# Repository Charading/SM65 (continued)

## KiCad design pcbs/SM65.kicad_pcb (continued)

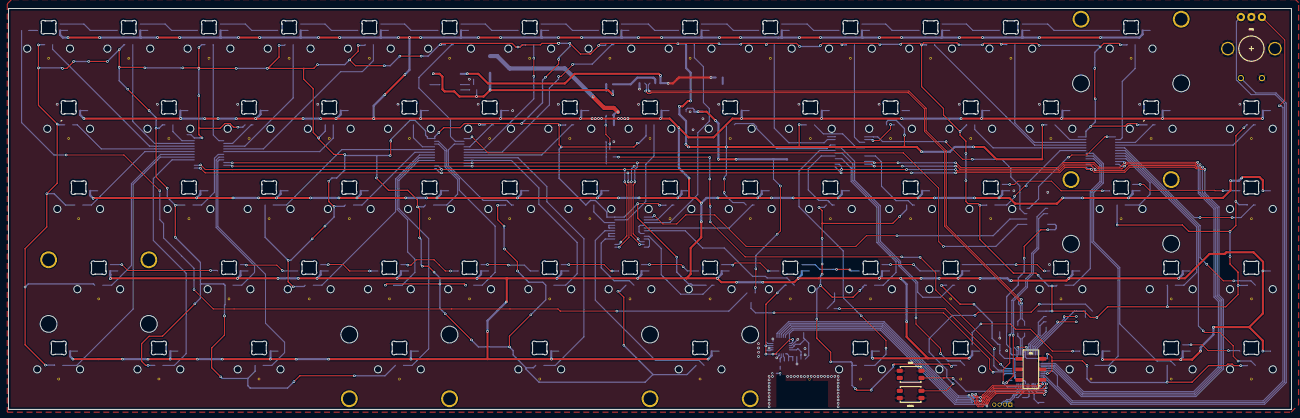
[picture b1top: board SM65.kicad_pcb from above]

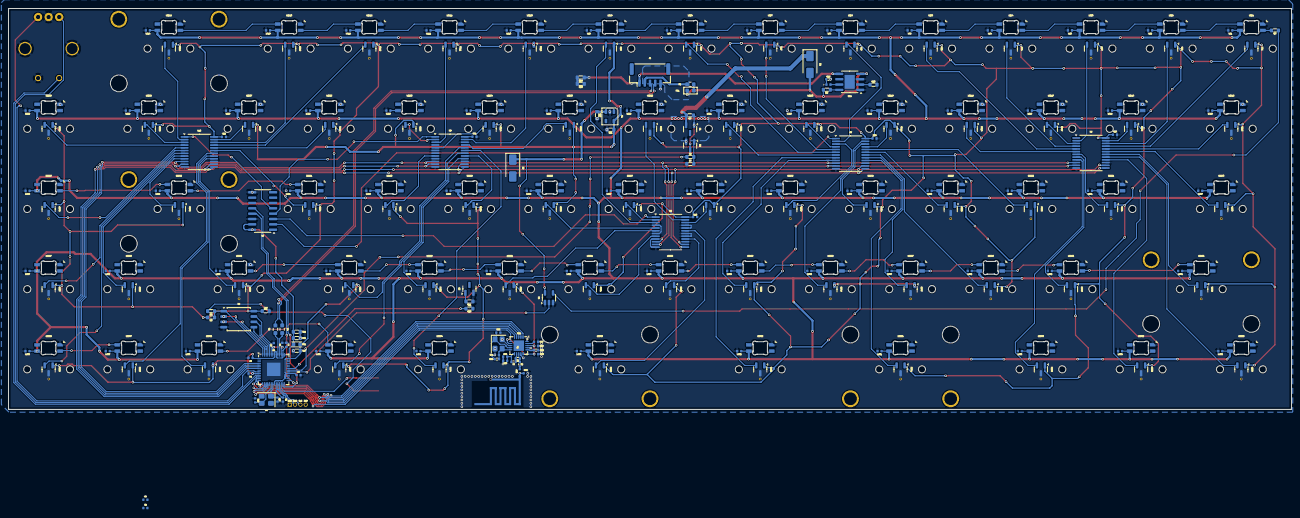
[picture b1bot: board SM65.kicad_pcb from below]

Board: 2 copper layers, 304.8 x 95.3 mm, 285 parts (281 on the bottom side), 207 nets.

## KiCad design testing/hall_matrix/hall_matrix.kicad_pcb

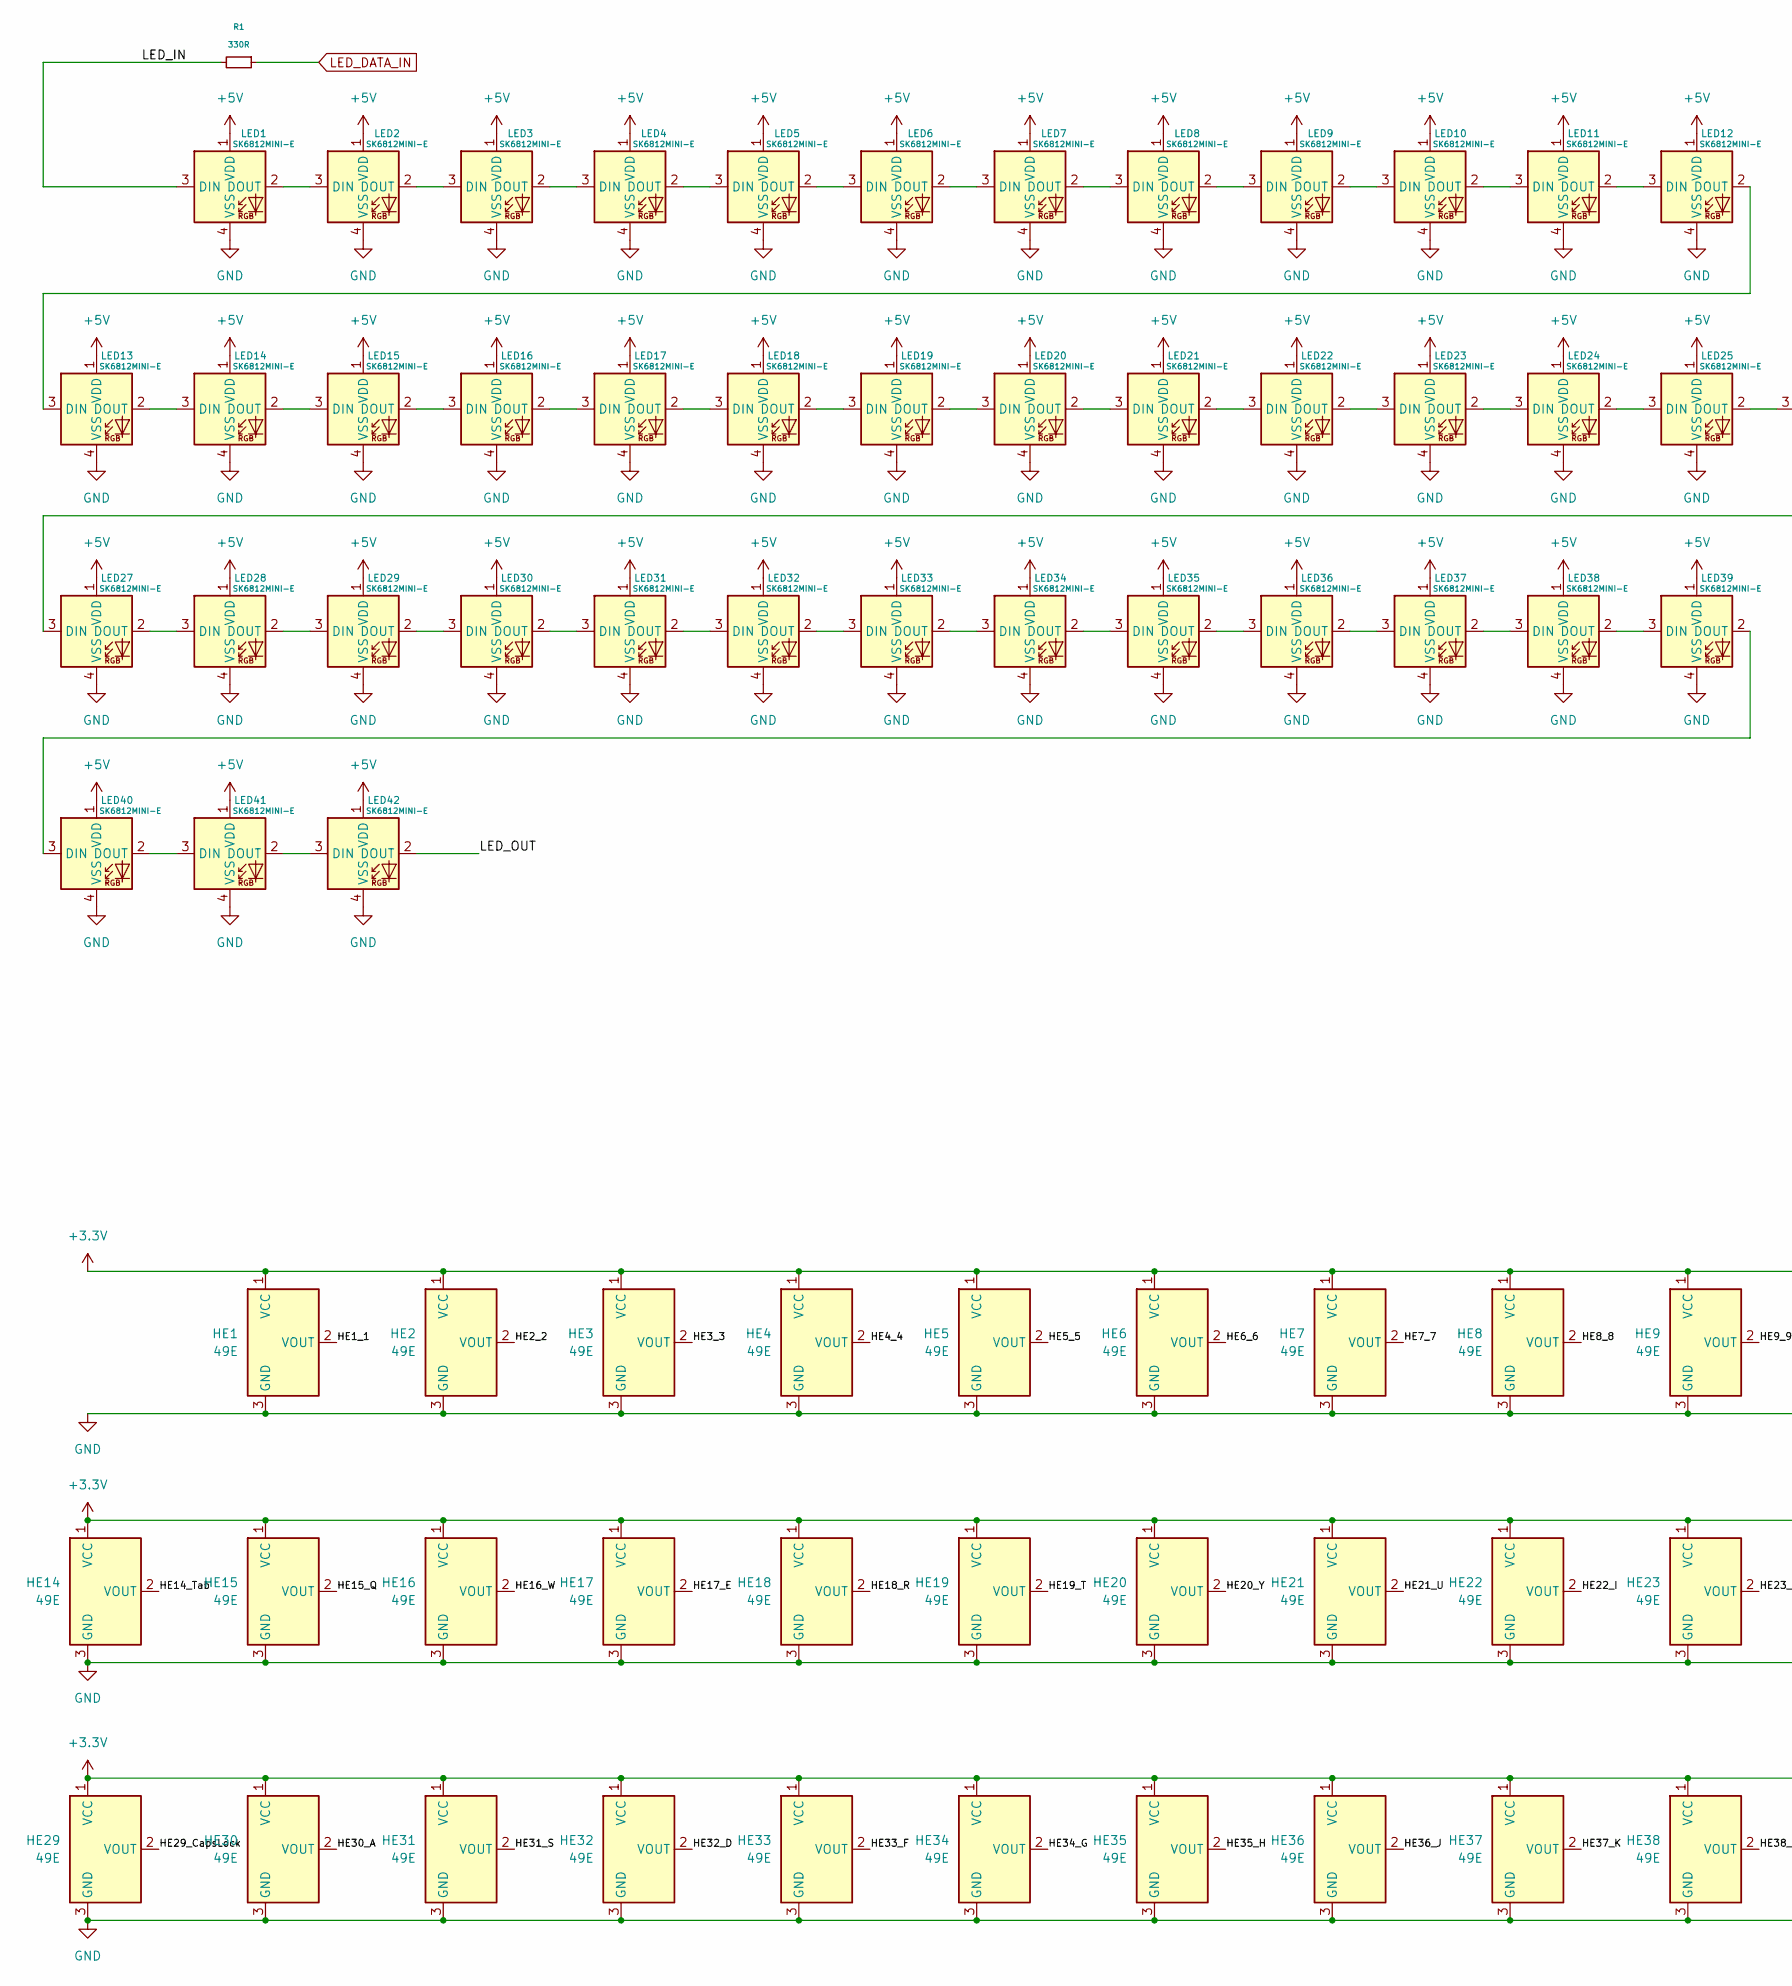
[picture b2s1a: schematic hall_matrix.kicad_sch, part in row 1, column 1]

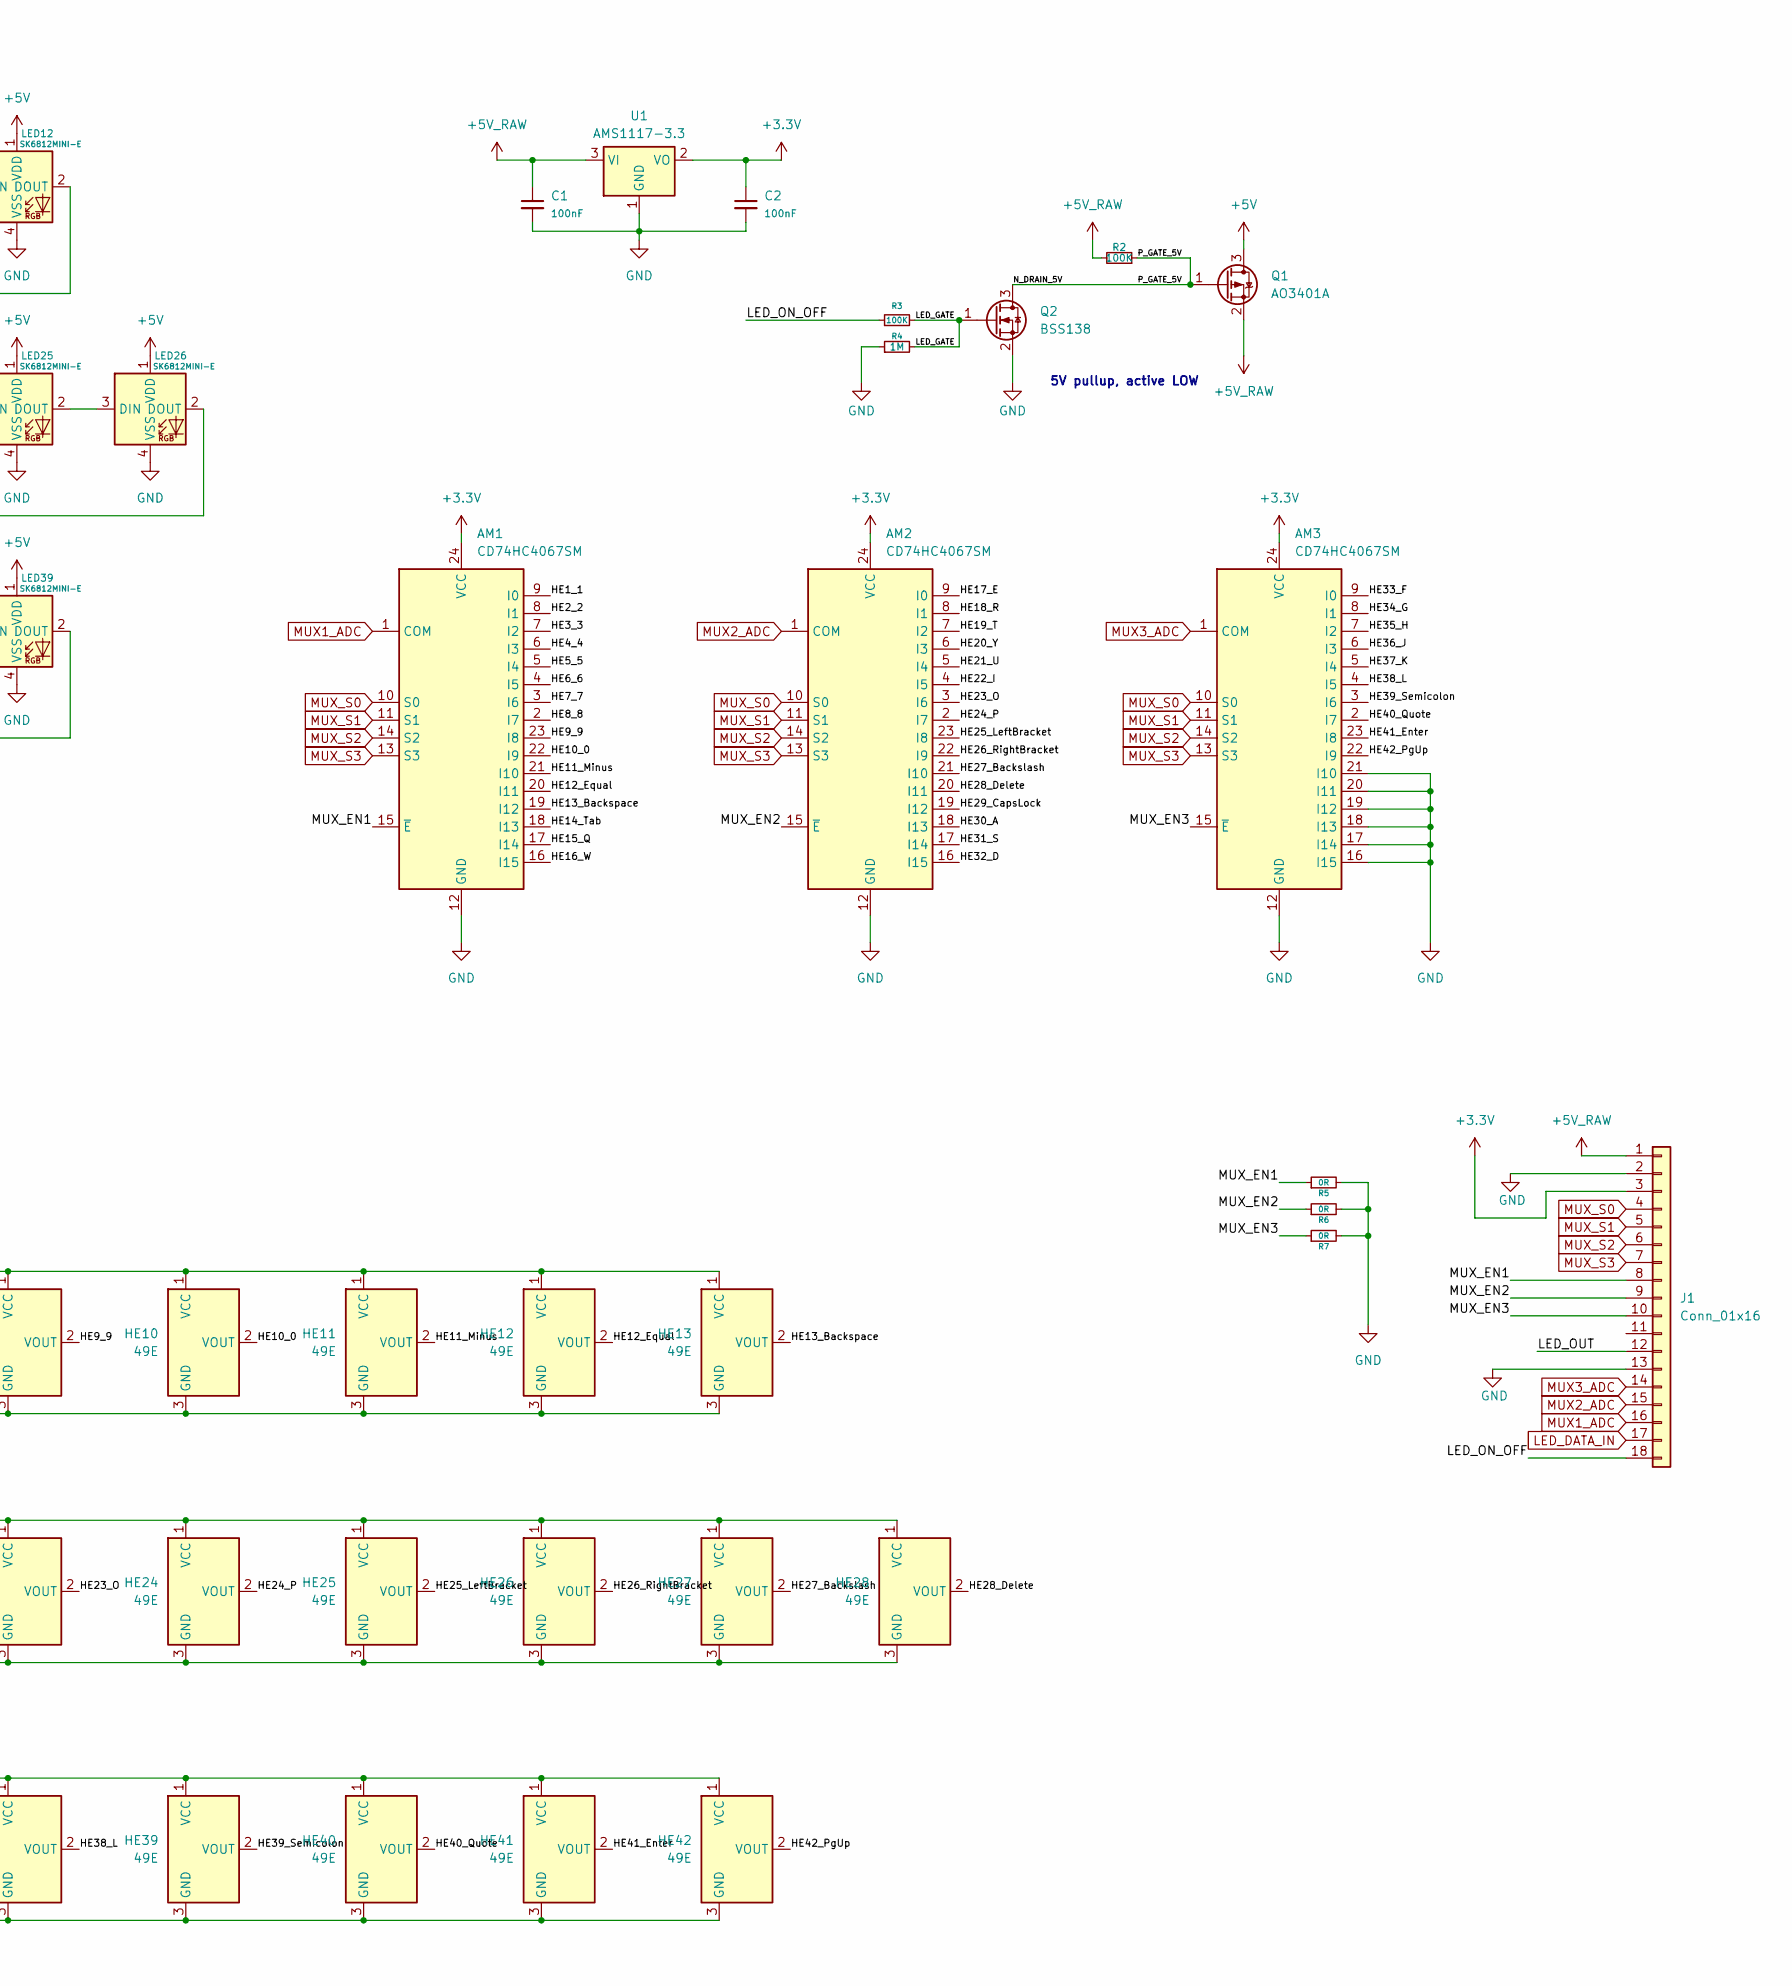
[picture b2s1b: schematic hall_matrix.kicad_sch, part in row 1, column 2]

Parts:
AM1, AM2, AM3: CD74HC4067SM; SSOP-24_5.3x8.2mm_P0.65mm
C1, C2: 100nF; C_0603
HE1, HE2, HE3, HE4, HE5, HE6, HE7, HE8, HE9, HE10, HE11, HE12, HE13, HE14, HE15, HE16, HE17, HE18, HE19, HE20, HE21, HE22, HE23, HE24, HE25, HE26, HE27, HE28, HE29, HE30, HE31, HE32, HE33, HE34, HE35, HE36, HE37, HE38, HE39, HE40, HE41, HE42: 49E; SW_MX_HE_90deg_1u_4layer; LCSC C7420984
J1: Conn_01x16; PinHeader_1x18_P2.54mm_Vertical
LED1, LED2, LED3, LED4, LED5, LED6, LED7, LED8, LED9, LED10, LED11, LED12, LED13, LED14, LED15, LED16, LED17, LED18, LED19, LED20, LED21, LED22, LED23, LED24, LED25, LED26, LED27, LED28, LED29, LED30, LED31, LED32, LED33, LED34, LED35, LED36, LED37, LED38, LED39, LED40, LED41, LED42: SK6812MINI-E; LED_6028R; LCSC C5149201
Q1: AO3401A; SOT-23
Q2: BSS138; SOT-23
R1: 330R; R_0603
R2, R3: 100K; R_0603
R4: 1M; R_0603
R5, R6, R7: 0R; R_0603
U1: AMS1117-3.3; SOT-223-3_TabPin2

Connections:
+3.3V: AM1.24 (VCC), AM2.24 (VCC), AM3.24 (VCC), C2.1, HE1.1 (VCC), HE2.1 (VCC), HE3.1 (VCC), HE4.1 (VCC), HE5.1 (VCC), HE6.1 (VCC), HE7.1 (VCC), HE8.1 (VCC), HE9.1 (VCC), HE10.1 (VCC), HE11.1 (VCC), HE12.1 (VCC), HE13.1 (VCC), HE14.1 (VCC), HE15.1 (VCC), HE16.1 (VCC), HE17.1 (VCC), HE18.1 (VCC), HE19.1 (VCC), HE20.1 (VCC), HE21.1 (VCC), HE22.1 (VCC), HE23.1 (VCC), HE24.1 (VCC), HE25.1 (VCC), HE26.1 (VCC), HE27.1 (VCC), HE28.1 (VCC), HE29.1 (VCC), HE30.1 (VCC), HE31.1 (VCC), HE32.1 (VCC), HE33.1 (VCC), HE34.1 (VCC), HE35.1 (VCC), HE36.1 (VCC), HE37.1 (VCC), HE38.1 (VCC), HE39.1 (VCC), HE40.1 (VCC), HE41.1 (VCC), HE42.1 (VCC), J1.3, U1.2 (VO)
+5V: LED1.1 (VDD), LED2.1 (VDD), LED3.1 (VDD), LED4.1 (VDD), LED5.1 (VDD), LED6.1 (VDD), LED7.1 (VDD), LED8.1 (VDD), LED9.1 (VDD), LED10.1 (VDD), LED11.1 (VDD), LED12.1 (VDD), LED13.1 (VDD), LED14.1 (VDD), LED15.1 (VDD), LED16.1 (VDD), LED17.1 (VDD), LED18.1 (VDD), LED19.1 (VDD), LED20.1 (VDD), LED21.1 (VDD), LED22.1 (VDD), LED23.1 (VDD), LED24.1 (VDD), LED25.1 (VDD), LED26.1 (VDD), LED27.1 (VDD), LED28.1 (VDD), LED29.1 (VDD), LED30.1 (VDD), LED31.1 (VDD), LED32.1 (VDD), LED33.1 (VDD), LED34.1 (VDD), LED35.1 (VDD), LED36.1 (VDD), LED37.1 (VDD), LED38.1 (VDD), LED39.1 (VDD), LED40.1 (VDD), LED41.1 (VDD), LED42.1 (VDD), Q1.3 (D)
+5V_RAW: C1.1, J1.1, Q1.2 (S), R2.2, U1.3 (VI)
/HE1_1: AM1.9 (I0), HE1.2 (VOUT)
/HE2_2: AM1.8 (I1), HE2.2 (VOUT)
/HE3_3: AM1.7 (I2), HE3.2 (VOUT)
/HE4_4: AM1.6 (I3), HE4.2 (VOUT)
/HE5_5: AM1.5 (I4), HE5.2 (VOUT)
/HE6_6: AM1.4 (I5), HE6.2 (VOUT)
/HE7_7: AM1.3 (I6), HE7.2 (VOUT)
/HE8_8: AM1.2 (I7), HE8.2 (VOUT)
/HE9_9: AM1.23 (I8), HE9.2 (VOUT)
/HE10_0: AM1.22 (I9), HE10.2 (VOUT)
/HE11_Minus: AM1.21 (I10), HE11.2 (VOUT)
/HE12_Equal: AM1.20 (I11), HE12.2 (VOUT)
/HE13_Backspace: AM1.19 (I12), HE13.2 (VOUT)
/HE14_Tab: AM1.18 (I13), HE14.2 (VOUT)
/HE15_Q: AM1.17 (I14), HE15.2 (VOUT)
/HE16_W: AM1.16 (I15), HE16.2 (VOUT)
/HE17_E: AM2.9 (I0), HE17.2 (VOUT)
/HE18_R: AM2.8 (I1), HE18.2 (VOUT)
/HE19_T: AM2.7 (I2), HE19.2 (VOUT)
/HE20_Y: AM2.6 (I3), HE20.2 (VOUT)
/HE21_U: AM2.5 (I4), HE21.2 (VOUT)
/HE22_I: AM2.4 (I5), HE22.2 (VOUT)
/HE23_O: AM2.3 (I6), HE23.2 (VOUT)
/HE24_P: AM2.2 (I7), HE24.2 (VOUT)
/HE25_LeftBracket: AM2.23 (I8), HE25.2 (VOUT)
/HE26_RightBracket: AM2.22 (I9), HE26.2 (VOUT)
/HE27_Backslash: AM2.21 (I10), HE27.2 (VOUT)
/HE28_Delete: AM2.20 (I11), HE28.2 (VOUT)
/HE29_CapsLock: AM2.19 (I12), HE29.2 (VOUT)
/HE30_A: AM2.18 (I13), HE30.2 (VOUT)
/HE31_S: AM2.17 (I14), HE31.2 (VOUT)
/HE32_D: AM2.16 (I15), HE32.2 (VOUT)
/HE33_F: AM3.9 (I0), HE33.2 (VOUT)
/HE34_G: AM3.8 (I1), HE34.2 (VOUT)
/HE35_H: AM3.7 (I2), HE35.2 (VOUT)
/HE36_J: AM3.6 (I3), HE36.2 (VOUT)
/HE37_K: AM3.5 (I4), HE37.2 (VOUT)
/HE38_L: AM3.4 (I5), HE38.2 (VOUT)
/HE39_Semicolon: AM3.3 (I6), HE39.2 (VOUT)
/HE40_Quote: AM3.2 (I7), HE40.2 (VOUT)
/HE41_Enter: AM3.23 (I8), HE41.2 (VOUT)
/HE42_PgUp: AM3.22 (I9), HE42.2 (VOUT)
/LED_GATE: Q2.1 (G), R3.2, R4.2
/LED_IN: LED1.3 (DIN), R1.2
/LED_ON_OFF: J1.18, R3.1
/LED_OUT: J1.12, LED42.2 (DOUT)
/MUX_EN1: AM1.15 (~E), J1.8, R5.1
/MUX_EN2: AM2.15 (~E), J1.9, R6.1
/MUX_EN3: AM3.15 (~E), J1.10, R7.1
/N_DRAIN_5V: Q1.1 (G), Q2.3 (D), R2.1
GND: AM1.12 (GND), AM2.12 (GND), AM3.12 (GND), AM3.16 (I15), AM3.17 (I14), AM3.18 (I13), AM3.19 (I12), AM3.20 (I11), AM3.21 (I10), C1.2, C2.2, HE1.3 (GND), HE2.3 (GND), HE3.3 (GND), HE4.3 (GND), HE5.3 (GND), HE6.3 (GND), HE7.3 (GND), HE8.3 (GND), HE9.3 (GND), HE10.3 (GND), HE11.3 (GND), HE12.3 (GND), HE13.3 (GND), HE14.3 (GND), HE15.3 (GND), HE16.3 (GND), HE17.3 (GND), HE18.3 (GND), HE19.3 (GND), HE20.3 (GND), HE21.3 (GND), HE22.3 (GND), HE23.3 (GND), HE24.3 (GND), HE25.3 (GND), HE26.3 (GND), HE27.3 (GND), HE28.3 (GND), HE29.3 (GND), HE30.3 (GND), HE31.3 (GND), HE32.3 (GND), HE33.3 (GND), HE34.3 (GND), HE35.3 (GND), HE36.3 (GND), HE37.3 (GND), HE38.3 (GND), HE39.3 (GND), HE40.3 (GND), HE41.3 (GND), HE42.3 (GND), J1.2, J1.13, LED1.4 (VSS), LED2.4 (VSS), LED3.4 (VSS), LED4.4 (VSS), LED5.4 (VSS), LED6.4 (VSS), LED7.4 (VSS), LED8.4 (VSS), LED9.4 (VSS), LED10.4 (VSS), LED11.4 (VSS), LED12.4 (VSS), LED13.4 (VSS), LED14.4 (VSS), LED15.4 (VSS), LED16.4 (VSS), LED17.4 (VSS), LED18.4 (VSS), LED19.4 (VSS), LED20.4 (VSS), LED21.4 (VSS), LED22.4 (VSS), LED23.4 (VSS), LED24.4 (VSS), LED25.4 (VSS), LED26.4 (VSS), LED27.4 (VSS), LED28.4 (VSS), LED29.4 (VSS), LED30.4 (VSS), LED31.4 (VSS), LED32.4 (VSS), LED33.4 (VSS), LED34.4 (VSS), LED35.4 (VSS), LED36.4 (VSS), LED37.4 (VSS), LED38.4 (VSS), LED39.4 (VSS), LED40.4 (VSS), LED41.4 (VSS), LED42.4 (VSS), Q2.2 (S), R4.1, R5.2, R6.2, R7.2, U1.1 (GND)
LED_DATA_IN: J1.17, R1.1
MUX1_ADC: AM1.1 (COM), J1.16
MUX2_ADC: AM2.1 (COM), J1.15
MUX3_ADC: AM3.1 (COM), J1.14
MUX_S0: AM1.10 (S0), AM2.10 (S0), AM3.10 (S0), J1.4
MUX_S1: AM1.11 (S1), AM2.11 (S1), AM3.11 (S1), J1.5
MUX_S2: AM1.14 (S2), AM2.14 (S2), AM3.14 (S2), J1.6
MUX_S3: AM1.13 (S3), AM2.13 (S3), AM3.13 (S3), J1.7
unnamed: LED1.2 (DOUT), LED2.3 (DIN)
unnamed: LED2.2 (DOUT), LED3.3 (DIN)
unnamed: LED3.2 (DOUT), LED4.3 (DIN)
unnamed: LED4.2 (DOUT), LED5.3 (DIN)
unnamed: LED5.2 (DOUT), LED6.3 (DIN)
unnamed: LED6.2 (DOUT), LED7.3 (DIN)
unnamed: LED7.2 (DOUT), LED8.3 (DIN)
unnamed: LED8.2 (DOUT), LED9.3 (DIN)
unnamed: LED9.2 (DOUT), LED10.3 (DIN)
unnamed: LED10.2 (DOUT), LED11.3 (DIN)
unnamed: LED11.2 (DOUT), LED12.3 (DIN)
unnamed: LED12.2 (DOUT), LED13.3 (DIN)
unnamed: LED13.2 (DOUT), LED14.3 (DIN)
unnamed: LED14.2 (DOUT), LED15.3 (DIN)
unnamed: LED15.2 (DOUT), LED16.3 (DIN)
unnamed: LED16.2 (DOUT), LED17.3 (DIN)
unnamed: LED17.2 (DOUT), LED18.3 (DIN)
unnamed: LED18.2 (DOUT), LED19.3 (DIN)
unnamed: LED19.2 (DOUT), LED20.3 (DIN)
unnamed: LED20.2 (DOUT), LED21.3 (DIN)
unnamed: LED21.2 (DOUT), LED22.3 (DIN)
unnamed: LED22.2 (DOUT), LED23.3 (DIN)
unnamed: LED23.2 (DOUT), LED24.3 (DIN)
unnamed: LED24.2 (DOUT), LED25.3 (DIN)
unnamed: LED25.2 (DOUT), LED26.3 (DIN)
unnamed: LED26.2 (DOUT), LED27.3 (DIN)
unnamed: LED27.2 (DOUT), LED28.3 (DIN)
unnamed: LED28.2 (DOUT), LED29.3 (DIN)
unnamed: LED29.2 (DOUT), LED30.3 (DIN)
unnamed: LED30.2 (DOUT), LED31.3 (DIN)
unnamed: LED31.2 (DOUT), LED32.3 (DIN)
unnamed: LED32.2 (DOUT), LED33.3 (DIN)
unnamed: LED33.2 (DOUT), LED34.3 (DIN)
unnamed: LED34.2 (DOUT), LED35.3 (DIN)
unnamed: LED35.2 (DOUT), LED36.3 (DIN)
unnamed: LED36.2 (DOUT), LED37.3 (DIN)
unnamed: LED37.2 (DOUT), LED38.3 (DIN)
unnamed: LED38.2 (DOUT), LED39.3 (DIN)
unnamed: LED39.2 (DOUT), LED40.3 (DIN)
unnamed: LED40.2 (DOUT), LED41.3 (DIN)
unnamed: LED41.2 (DOUT), LED42.3 (DIN)

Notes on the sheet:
5V pullup, active LOW

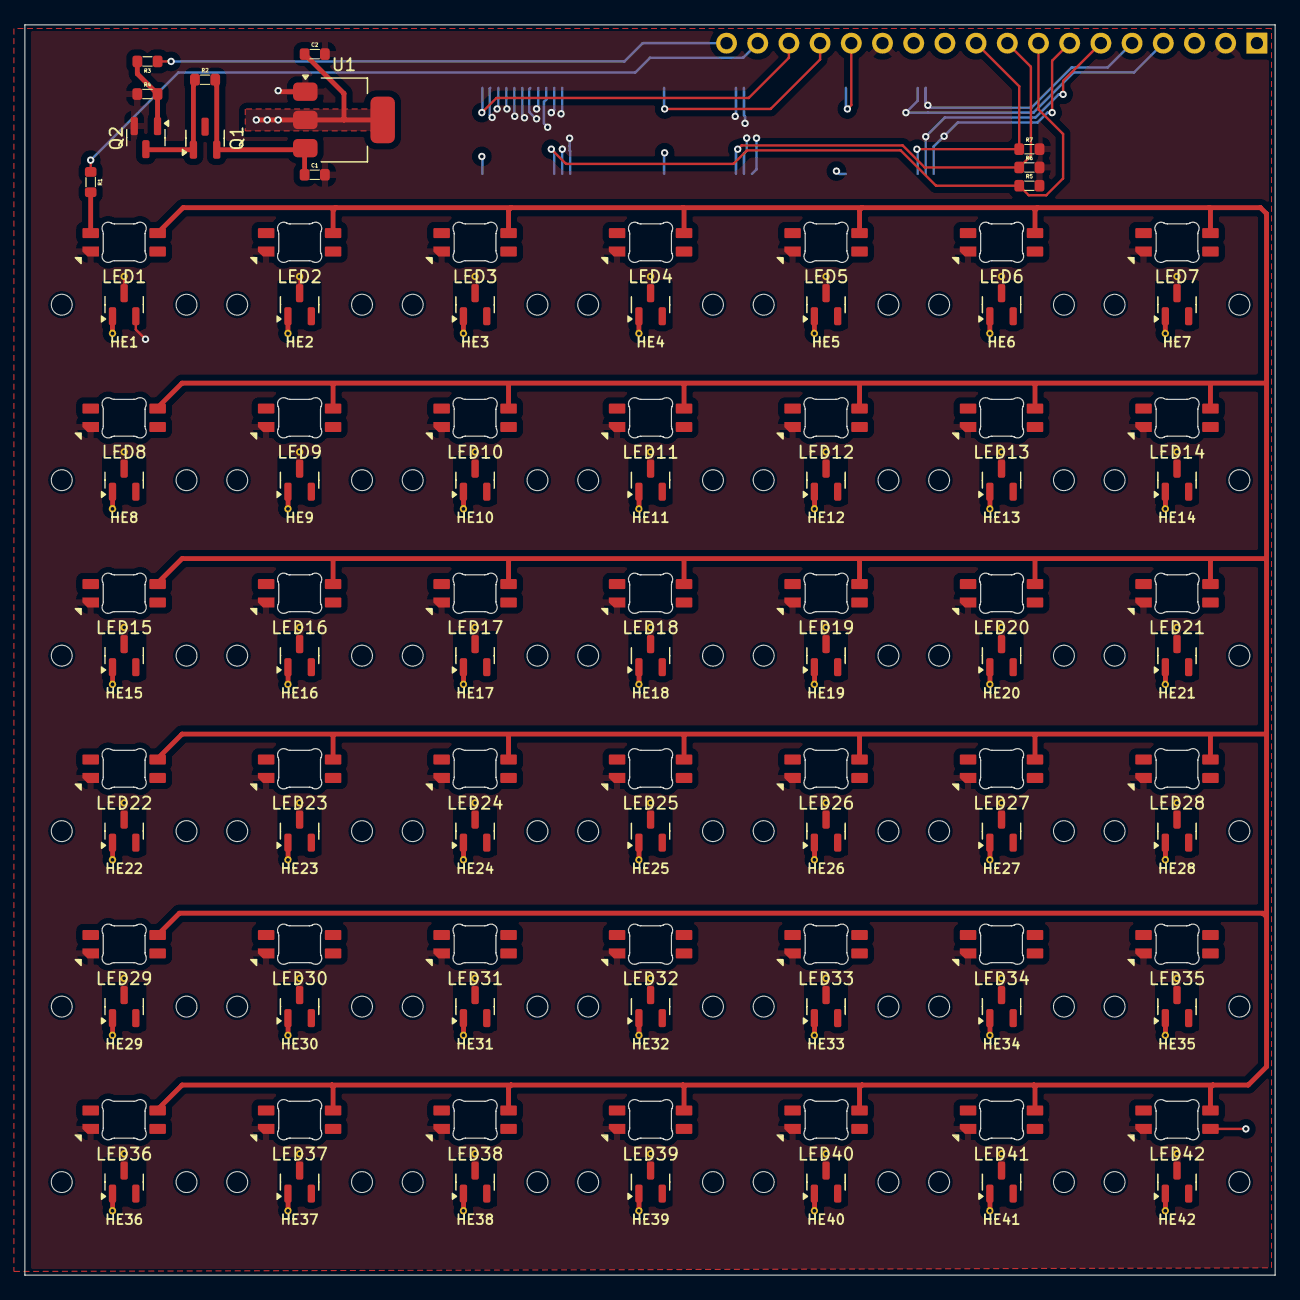
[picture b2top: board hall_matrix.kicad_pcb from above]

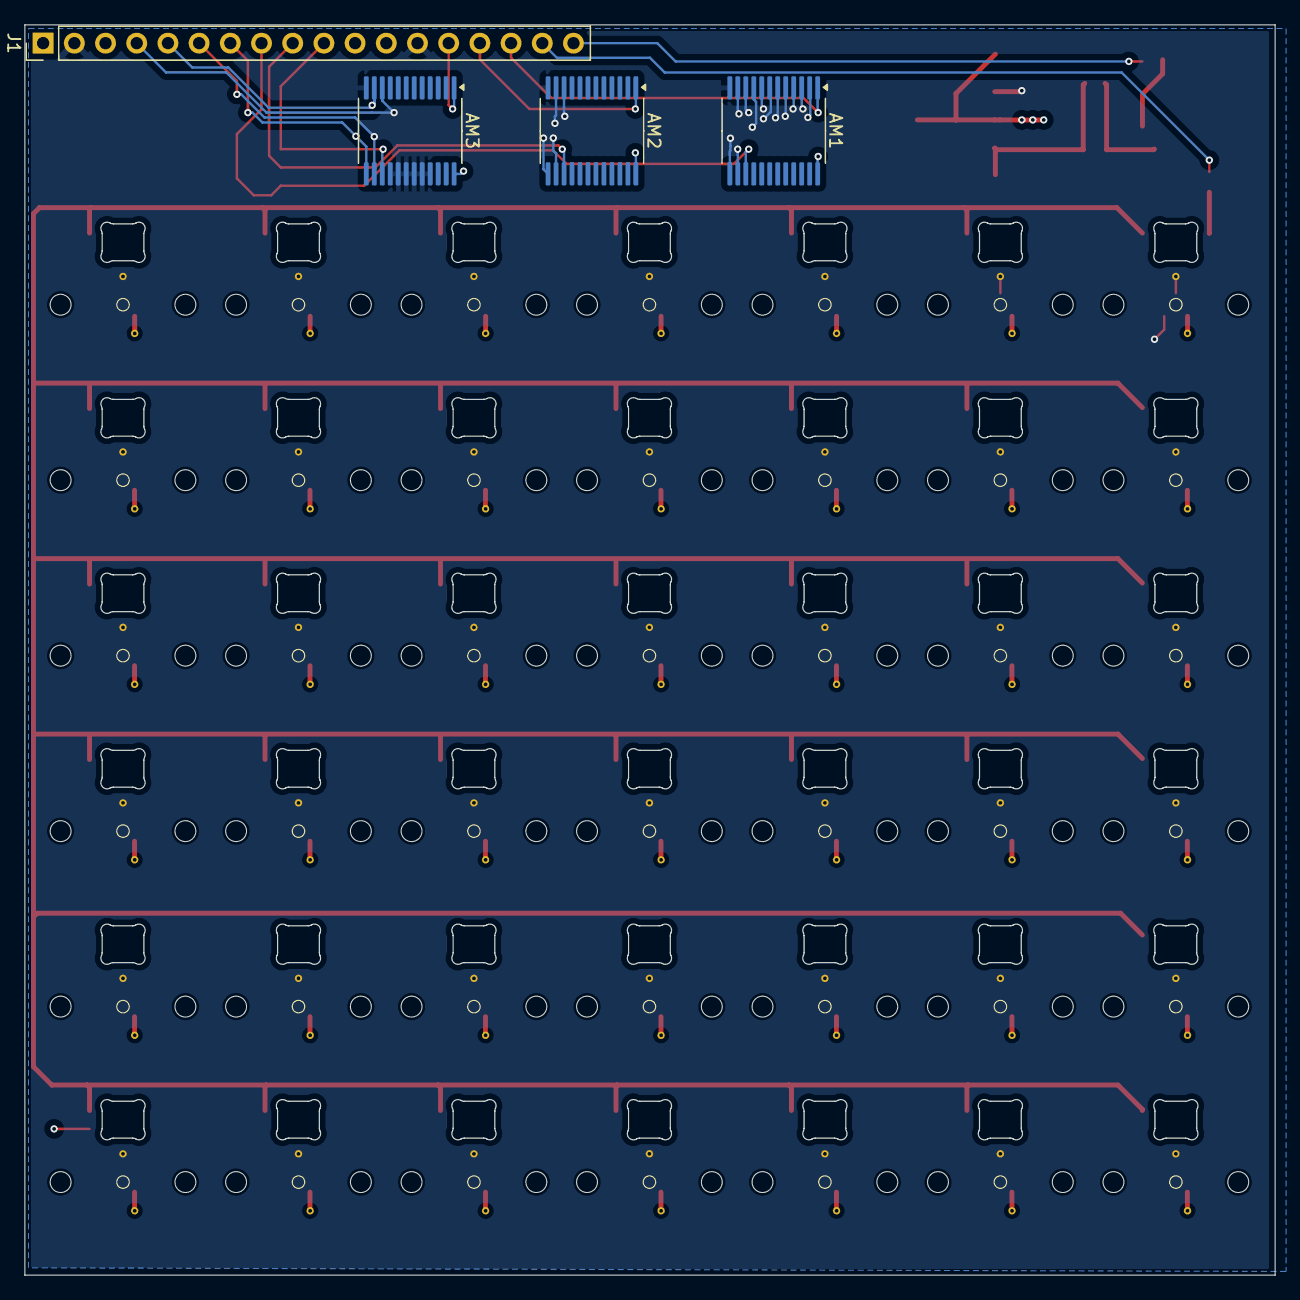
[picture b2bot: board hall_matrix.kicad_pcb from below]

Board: 4 copper layers, 101.8 x 101.8 mm, 100 parts (4 on the bottom side), 103 nets.

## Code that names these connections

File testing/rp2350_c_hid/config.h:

#define MUX_S0 10
#define MUX_S1 11
#define MUX_S2 12
#define MUX_S3 13

#define MUX1_PIN 40  // ADC0 (GP40)
#define MUX2_PIN 45  // ADC1 (GP41)
#define MUX3_PIN 46  // ADC2 (GP42)
#define MUX4_PIN 47  // ADC3 (GP43)
#define MUX5_PIN 44  // ADC4 (GP44) - RP2350B only

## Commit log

2025-11-08 was testing rp2350 with hc4067
2025-11-08 new branch for rp2350 version
2025-11-09 usb enumerated, cdc working to print adc voltages
2025-11-10 experimenting with MCP3208 and 4+ HC4067's
2025-11-24 improved schematic
2025-11-28 pcb updated
